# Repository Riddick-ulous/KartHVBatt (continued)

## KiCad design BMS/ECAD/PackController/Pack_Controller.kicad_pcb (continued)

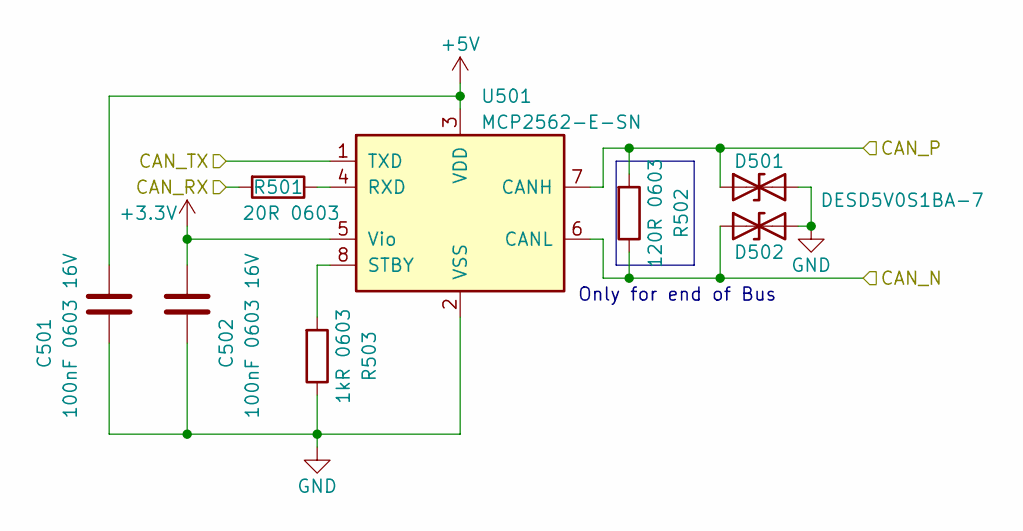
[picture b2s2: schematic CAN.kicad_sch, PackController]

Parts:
C501, C502: 100nF 0603 16V; C_0603_1608Metric_Pad1.08x0.95mm_HandSolder
D501, D502: DESD5V0S1BA-7; D_SOD-323
R501: 20R 0603; R_0603_1608Metric_Pad0.98x0.95mm_HandSolder
R502: 120R 0603; R_0603_1608Metric_Pad0.98x0.95mm_HandSolder
R503: 1kR 0603; R_0603_1608Metric_Pad0.98x0.95mm_HandSolder
U501: MCP2562-E-SN; SOIC-8_3.9x4.9mm_P1.27mm

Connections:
+3.3V: C502.2, U501.5 (Vio); also elsewhere on the board
+5V: C501.2, U501.3 (VDD); also elsewhere on the board
/CAN1/CAN_N: D502.1 (A1), R502.1, U501.6 (CANL); also elsewhere on the board
/CAN1/CAN_P: D501.1 (A1), R502.2, U501.7 (CANH); also elsewhere on the board
/CAN1/CAN_RX: R501.2; also elsewhere on the board
/CAN1/CAN_TX: U501.1 (TXD); also elsewhere on the board
GND: C501.1, C502.1, D501.2 (A2), D502.2 (A2), R503.1, U501.2 (VSS); also elsewhere on the board
unnamed: R501.1, U501.4 (RXD)
unnamed: R503.2, U501.8 (STBY)

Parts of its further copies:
C601, C602: 100nF 0603 16V; C_0603_1608Metric_Pad1.08x0.95mm_HandSolder
D601, D602: DESD5V0S1BA-7; D_SOD-323
R601: 20R 0603; R_0603_1608Metric_Pad0.98x0.95mm_HandSolder
R602: 120R 0603; R_0603_1608Metric_Pad0.98x0.95mm_HandSolder
R603: 1kR 0603; R_0603_1608Metric_Pad0.98x0.95mm_HandSolder
U601: MCP2562-E-SN; SOIC-8_3.9x4.9mm_P1.27mm

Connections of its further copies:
+3.3V: C602.2, U601.5 (Vio); also elsewhere on the board
+5V: C601.2, U601.3 (VDD); also elsewhere on the board
/CAN2/CAN_N: D602.1 (A1), R602.1, U601.6 (CANL); also elsewhere on the board
/CAN2/CAN_P: D601.1 (A1), R602.2, U601.7 (CANH); also elsewhere on the board
/CAN2/CAN_RX: R601.2; also elsewhere on the board
/CAN2/CAN_TX: U601.1 (TXD); also elsewhere on the board
GND: C601.1, C602.1, D601.2 (A2), D602.2 (A2), R603.1, U601.2 (VSS); also elsewhere on the board
unnamed: R601.1, U601.4 (RXD)
unnamed: R603.2, U601.8 (STBY)

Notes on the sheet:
Only for end of Bus

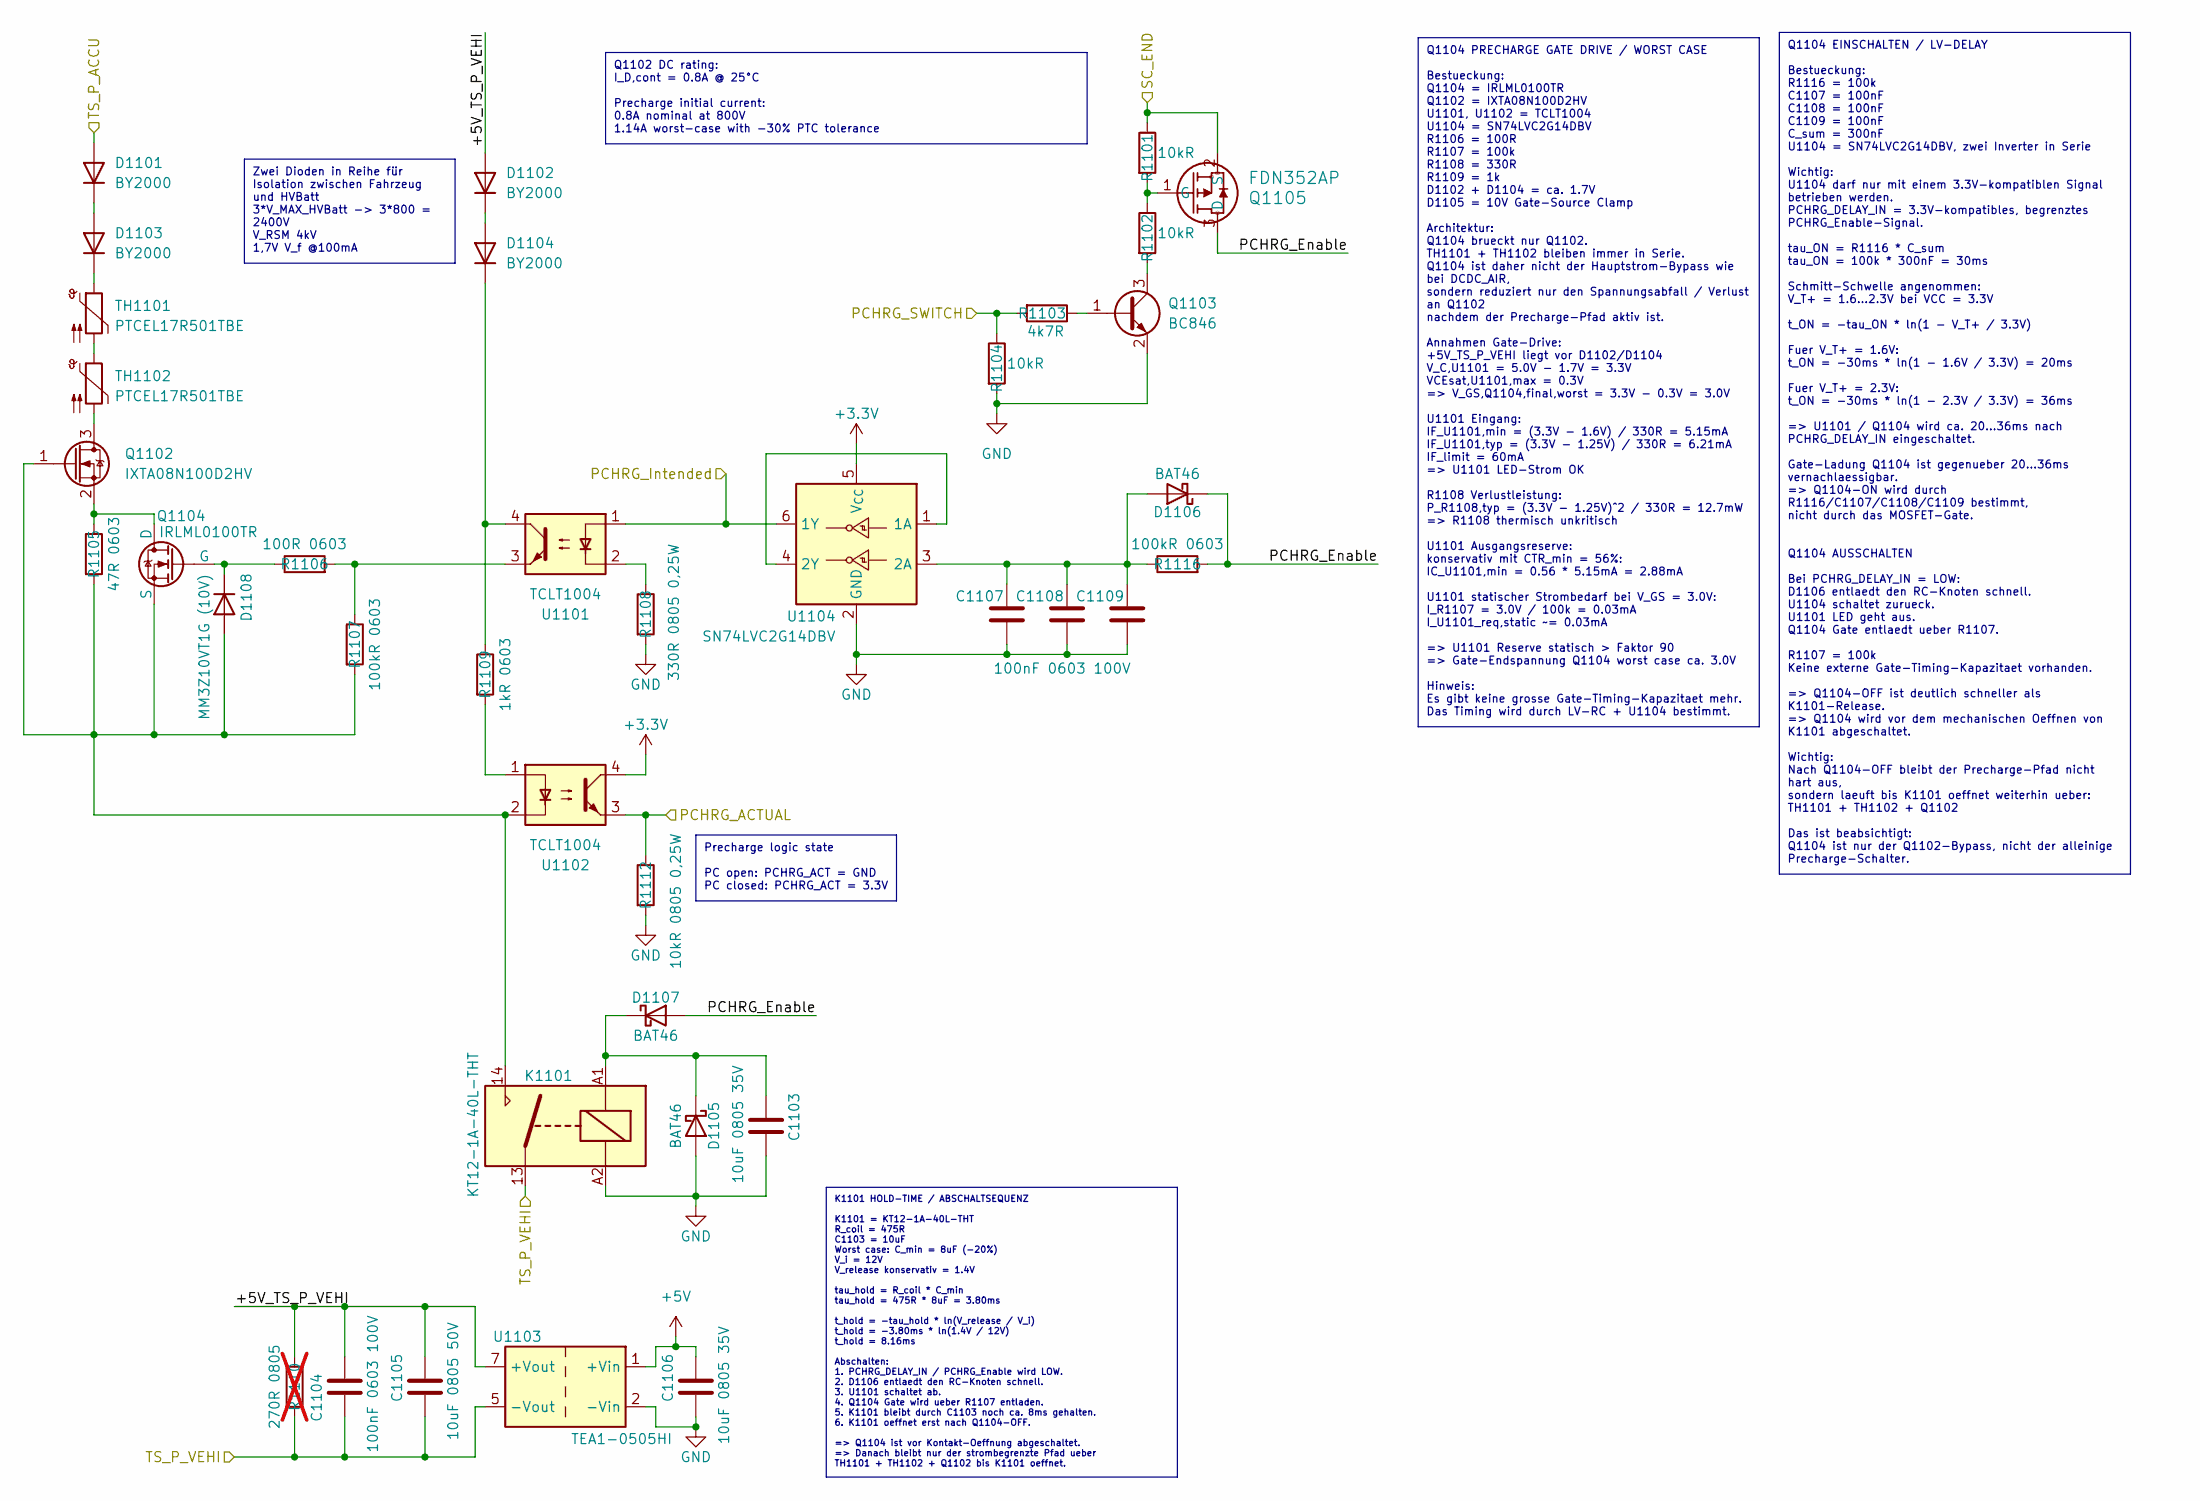
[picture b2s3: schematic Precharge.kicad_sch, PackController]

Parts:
C1103, C1106: 10uF 0805 35V; C_0805_2012Metric
C1104, C1107, C1108, C1109: 100nF 0603 100V; C_0603_1608Metric_Pad1.08x0.95mm_HandSolder
C1105: 10uF 0805 50V; C_0805_2012Metric
D1101, D1102, D1103, D1104: BY2000; D_DO-201AE_P12.70mm_Horizontal
D1105, D1106, D1107: BAT46; D_SOD-123
D1108: MM3Z10VT1G (10V); D_SOD-323_HandSoldering; PartNr. MM3Z3V3T1G
K1101: KT12-1A-40L-THT; Meder_KT_Relay
Q1102: IXTA08N100D2HV; TO-263HV
Q1103: BC846; SOT-23
Q1104: IRLML0100TR; SOT-23-3
Q1105: FDN352AP; SOT-23
R1101, R1102, R1104: 10kR; R_0603_1608Metric
R1103: 4k7R; R_0603_1608Metric
R1105: 47R 0603; R_1206_3216Metric
R1106: 100R 0603; R_0603_1608Metric_Pad0.98x0.95mm_HandSolder
R1107, R1116: 100kR 0603; R_0603_1608Metric_Pad0.98x0.95mm_HandSolder
R1108: 330R 0805 0,25W; R_0805_2012Metric
R1109: 1kR 0603; R_0603_1608Metric_Pad0.98x0.95mm_HandSolder
R1110: 270R 0805; R_0805_2012Metric_Pad1.20x1.40mm_HandSolder; not fitted
R1112: 10kR 0805 0,25W; R_0805_2012Metric
TH1101, TH1102: PTCEL17R501TBE; RV_Disc_D16.5mm_W6.7mm_P7.5mm
U1101, U1102: TCLT1004; SOP-4_7.5x4.1mm_P2.54mm
U1103: TEA1-0505HI; Converter_DCDC_TRACO_TEA1-xxxxHI_THT
U1104: SN74LVC2G14DBV; SOT-23-6

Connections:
+3.3V: U1102.4, U1104.5 (V_{CC}); also elsewhere on the board
+5V: C1106.1, U1103.1 (+Vin); also elsewhere on the board
/AIR/SC_END: Q1105.2 (S), R1101.1; also elsewhere on the board
/MCU/PCHRG_ACTUAL: R1112.1, U1102.3; also elsewhere on the board
/MCU/PCHRG_SWITCH: R1103.2, R1104.1; also elsewhere on the board
/Precharge/+5V_TS_P_VEHI: C1104.2, C1105.1, D1102.2 (A), R1110.2, U1103.7 (+Vout)
/Precharge/PCHRG_Enable: D1106.1 (K), D1107.2 (A), Q1105.3 (D), R1116.2
/Precharge/PCHRG_Intended: U1101.1, U1104.6 (1Y); also elsewhere on the board
/TS_P_ACCU: D1101.2 (A); also elsewhere on the board
/TS_P_VEHI: C1104.1, C1105.2, K1101.13, R1110.1, U1103.5 (-Vout); also elsewhere on the board
GND: C1103.2, C1106.2, C1107.1, C1108.1, C1109.1, D1105.2 (A), K1101.A2, Q1103.2 (E), R1104.2, R1108.2, R1112.2, U1103.2 (-Vin), U1104.2 (GND); also elsewhere on the board
unnamed: D1101.1 (K), D1103.2 (A)
unnamed: D1102.1 (K), D1104.2 (A)
unnamed: D1103.1 (K), TH1101.1
unnamed: D1104.1 (K), R1109.1, U1101.4
unnamed: C1103.1, D1105.1 (K), D1107.1 (K), K1101.A1
unnamed: C1107.2, C1108.2, C1109.2, D1106.2 (A), R1116.1, U1104.3 (2A)
unnamed: D1108.2 (A), K1101.14, Q1102.1 (G), Q1104.3 (S), R1105.2, R1107.2, U1102.2
unnamed: D1108.1 (K), Q1104.2 (G), R1106.1
unnamed: Q1102.3 (D), TH1102.2
unnamed: Q1102.2 (S), Q1104.1 (D), R1105.1
unnamed: Q1103.1 (B), R1103.1
unnamed: Q1103.3 (C), R1102.2
unnamed: Q1105.1 (G), R1101.2, R1102.1
unnamed: R1106.2, R1107.1, U1101.3
unnamed: R1108.1, U1101.2
unnamed: R1109.2, U1102.1
unnamed: TH1101.2, TH1102.1
unnamed: U1104.1 (1A), U1104.4 (2Y)

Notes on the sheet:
Q1104 EINSCHALTEN / LV-DELAY Bestueckung: R1116 = 100k C1107 = 100nF C1108 = 100nF C1109 = 100nF C_sum = 300nF U1104 = SN74LVC2G14DBV, zwei Inverter in Serie Wichtig: U1104 darf nur mit einem 3.3V-kompatiblen Signal betrieben werden. PCHRG_DELAY_IN = 3.3V-kompatibles, begrenztes PCHRG_Enable-Signal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
Q1102 DC rating: I_D,cont = 0.8A @ 25°C Precharge initial current: 0.8A nominal at 800V 1.14A worst-case with -30% PTC tolerance
K1101 HOLD-TIME / ABSCHALTSEQUENZ K1101 = KT12-1A-40L-THT R_coil = 475R C1103 = 10uF Worst case: C_min = 8uF (-20%) V_i = 12V V_release konservativ = 1.4V tau_hold = R_coil * C_min tau_hold = 475R * 8uF = 3.80ms t_hold = -tau_hold * ln(V_release / V_i) t_hold = -3.80ms * ln(1.4V / 12V) t_hold = 8.1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
Q1104 PRECHARGE GATE DRIVE / WORST CASE Bestueckung: Q1104 = IRLML0100TR Q1102 = IXTA08N100D2HV U1101, U1102 = TCLT1004 U1104 = SN74LVC2G14DBV R1106 = 100R R1107 = 100k R1108 = 330R R1109 = 1k D1102 + D1104 = ca. 1.7V D1105 = 10V Gate-Source Clamp Architektur: Q1104 brueckt nur Q1102. TH1101 + TH11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
Zwei Dioden in Reihe für Isolation zwischen Fahrzeug und HVBatt 3*V_MAX_HVBatt -> 3*800 = 2400V V_RSM 4kV 1,7V V_f @100mA
Precharge logic state PC open: PCHRG_ACT = GND PC closed: PCHRG_ACT = 3.3V

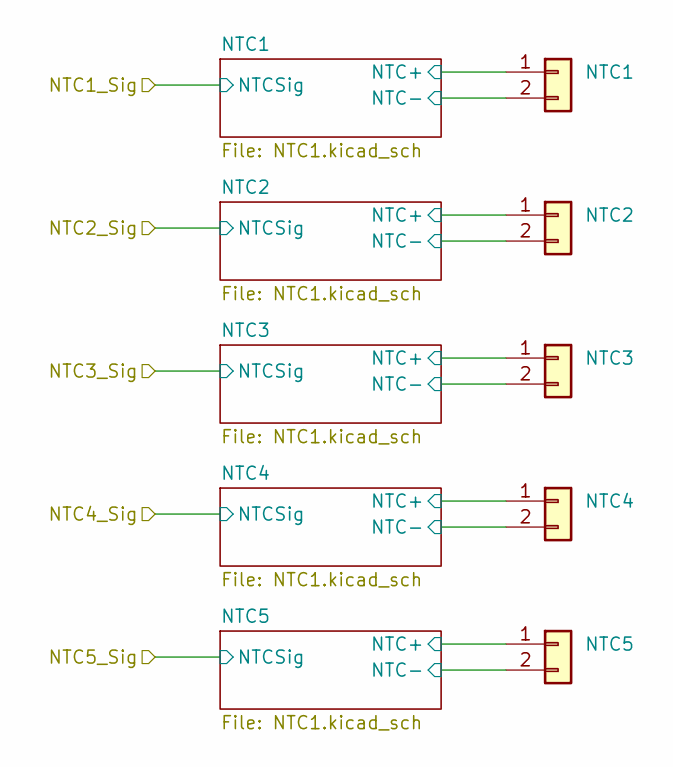
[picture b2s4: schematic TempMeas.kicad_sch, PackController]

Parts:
NTC1, NTC2, NTC3, NTC4, NTC5: Molex_Micro-Fit_3.0_43650-0215_1x02_P3.00mm_Vertical

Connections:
/TempMeas/NTC1/NTC+: NTC1.1; also elsewhere on the board
/TempMeas/NTC2/NTC+: NTC2.1; also elsewhere on the board
/TempMeas/NTC3/NTC+: NTC3.1; also elsewhere on the board
/TempMeas/NTC4/NTC+: NTC4.1; also elsewhere on the board
/TempMeas/NTC5/NTC+: NTC5.1; also elsewhere on the board
GND: NTC1.2, NTC2.2, NTC3.2, NTC4.2, NTC5.2; also elsewhere on the board

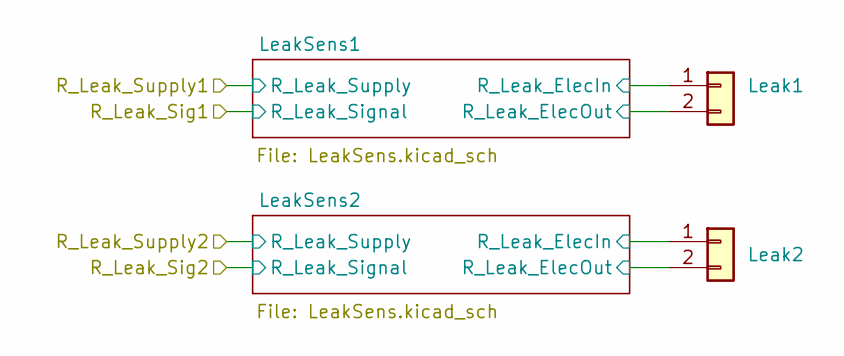
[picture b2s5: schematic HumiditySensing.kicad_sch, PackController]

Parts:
Leak1: Conn_01x02; Molex_Micro-Fit_3.0_43650-0215_1x02_P3.00mm_Vertical
Leak2: Molex_Micro-Fit_3.0_43650-0215_1x02_P3.00mm_Vertical

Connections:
/HumiditySensing/LeakSens1/R_Leak_ElecIn: Leak1.1; also elsewhere on the board
/HumiditySensing/LeakSens1/R_Leak_ElecOut: Leak1.2; also elsewhere on the board
/HumiditySensing/LeakSens2/R_Leak_ElecIn: Leak2.1; also elsewhere on the board
/HumiditySensing/LeakSens2/R_Leak_ElecOut: Leak2.2; also elsewhere on the board

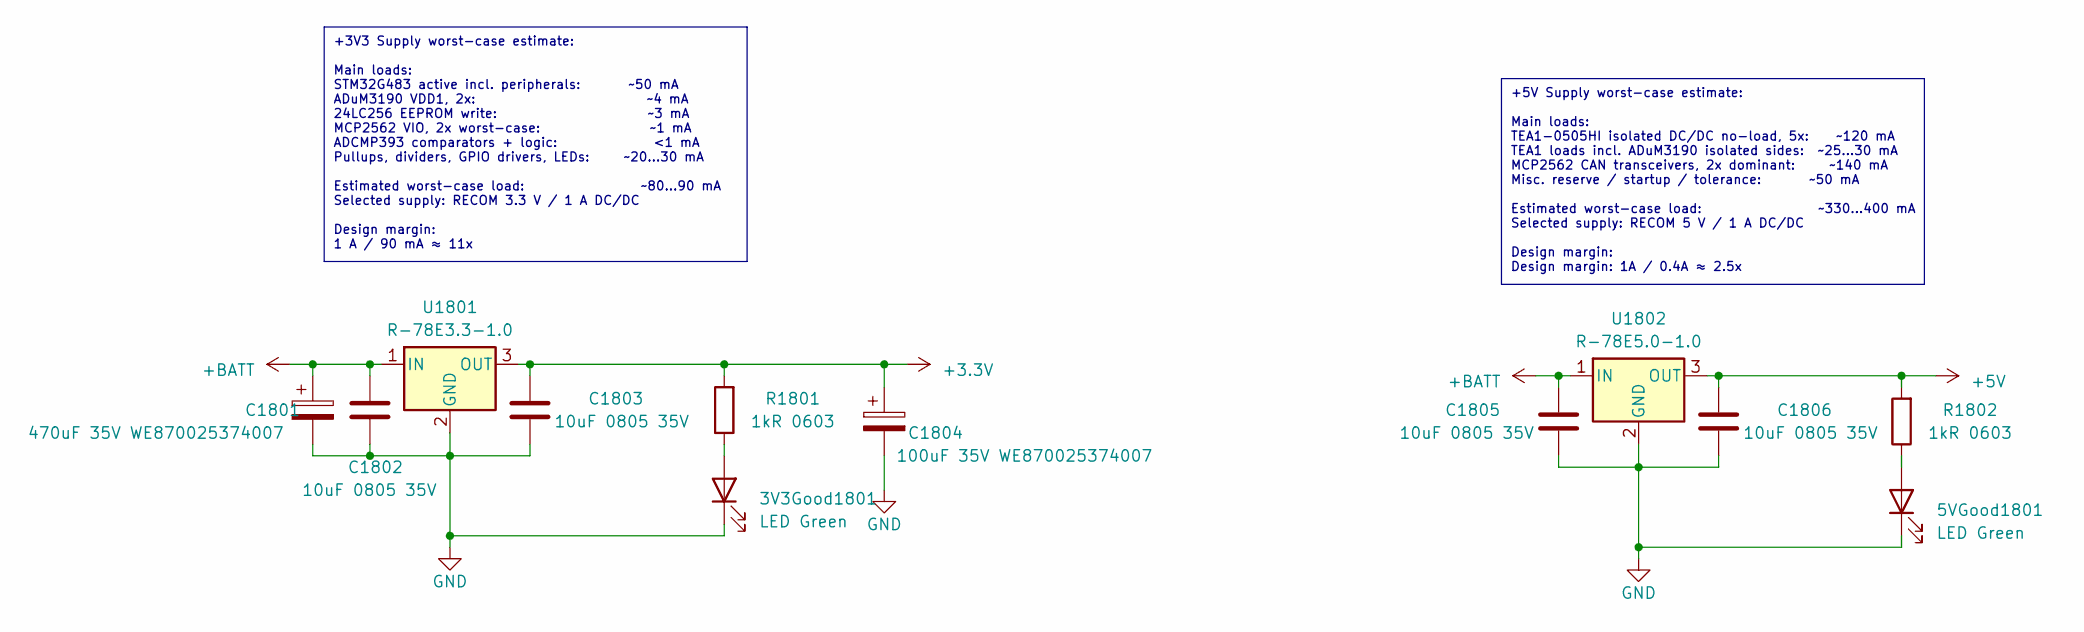
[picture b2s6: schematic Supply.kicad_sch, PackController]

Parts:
3V3Good1801, 5VGood1801: LED Green; LED_0805_2012Metric_Pad1.15x1.40mm_HandSolder
C1801: 470uF 35V WE870025374007; CP_Radial_D8.0mm_P3.50mm
C1802, C1803, C1805, C1806: 10uF 0805 35V; C_0805_2012Metric_Pad1.18x1.45mm_HandSolder
C1804: 100uF 35V WE870025374007; CP_Radial_D8.0mm_P3.50mm
R1801, R1802: 1kR 0603; R_0603_1608Metric_Pad0.98x0.95mm_HandSolder
U1801: R-78E3.3-1.0; Converter_DCDC_RECOM_R-78E-0.5_THT
U1802: R-78E5.0-1.0; Converter_DCDC_RECOM_R-78E-0.5_THT

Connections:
+3.3V: C1803.1, C1804.1, R1801.2, U1801.3 (OUT); also elsewhere on the board
+5V: C1806.1, R1802.2, U1802.3 (OUT); also elsewhere on the board
+BATT: C1801.1, C1802.1, C1805.1, U1801.1 (IN), U1802.1 (IN); also elsewhere on the board
GND: 3V3Good1801.1 (K), 5VGood1801.1 (K), C1801.2, C1802.2, C1803.2, C1804.2, C1805.2, C1806.2, U1801.2 (GND), U1802.2 (GND); also elsewhere on the board
unnamed: 3V3Good1801.2 (A), R1801.1
unnamed: 5VGood1801.2 (A), R1802.1

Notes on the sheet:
+3V3 Supply worst-case estimate: Main loads: STM32G483 active incl. peripherals: ~50 mA ADuM3190 VDD1, 2x: ~4 mA 24LC256 EEPROM write: ~3 mA MCP2562 VIO, 2x worst-case: ~1 mA ADCMP393 comparators + logic: <1 mA Pullups, dividers, GPIO drivers, LEDs: ~20...30 mA Estimated worst-case load: ~80...90 m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
+5V Supply worst-case estimate: Main loads: TEA1-0505HI isolated DC/DC no-load, 5x: ~120 mA TEA1 loads incl. ADuM3190 isolated sides: ~25...30 mA MCP2562 CAN transceivers, 2x dominant: ~140 mA Misc. reserve / startup / tolerance: ~50 mA Estimated worst-case load: ~330...400 mA Selected supply: RECO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

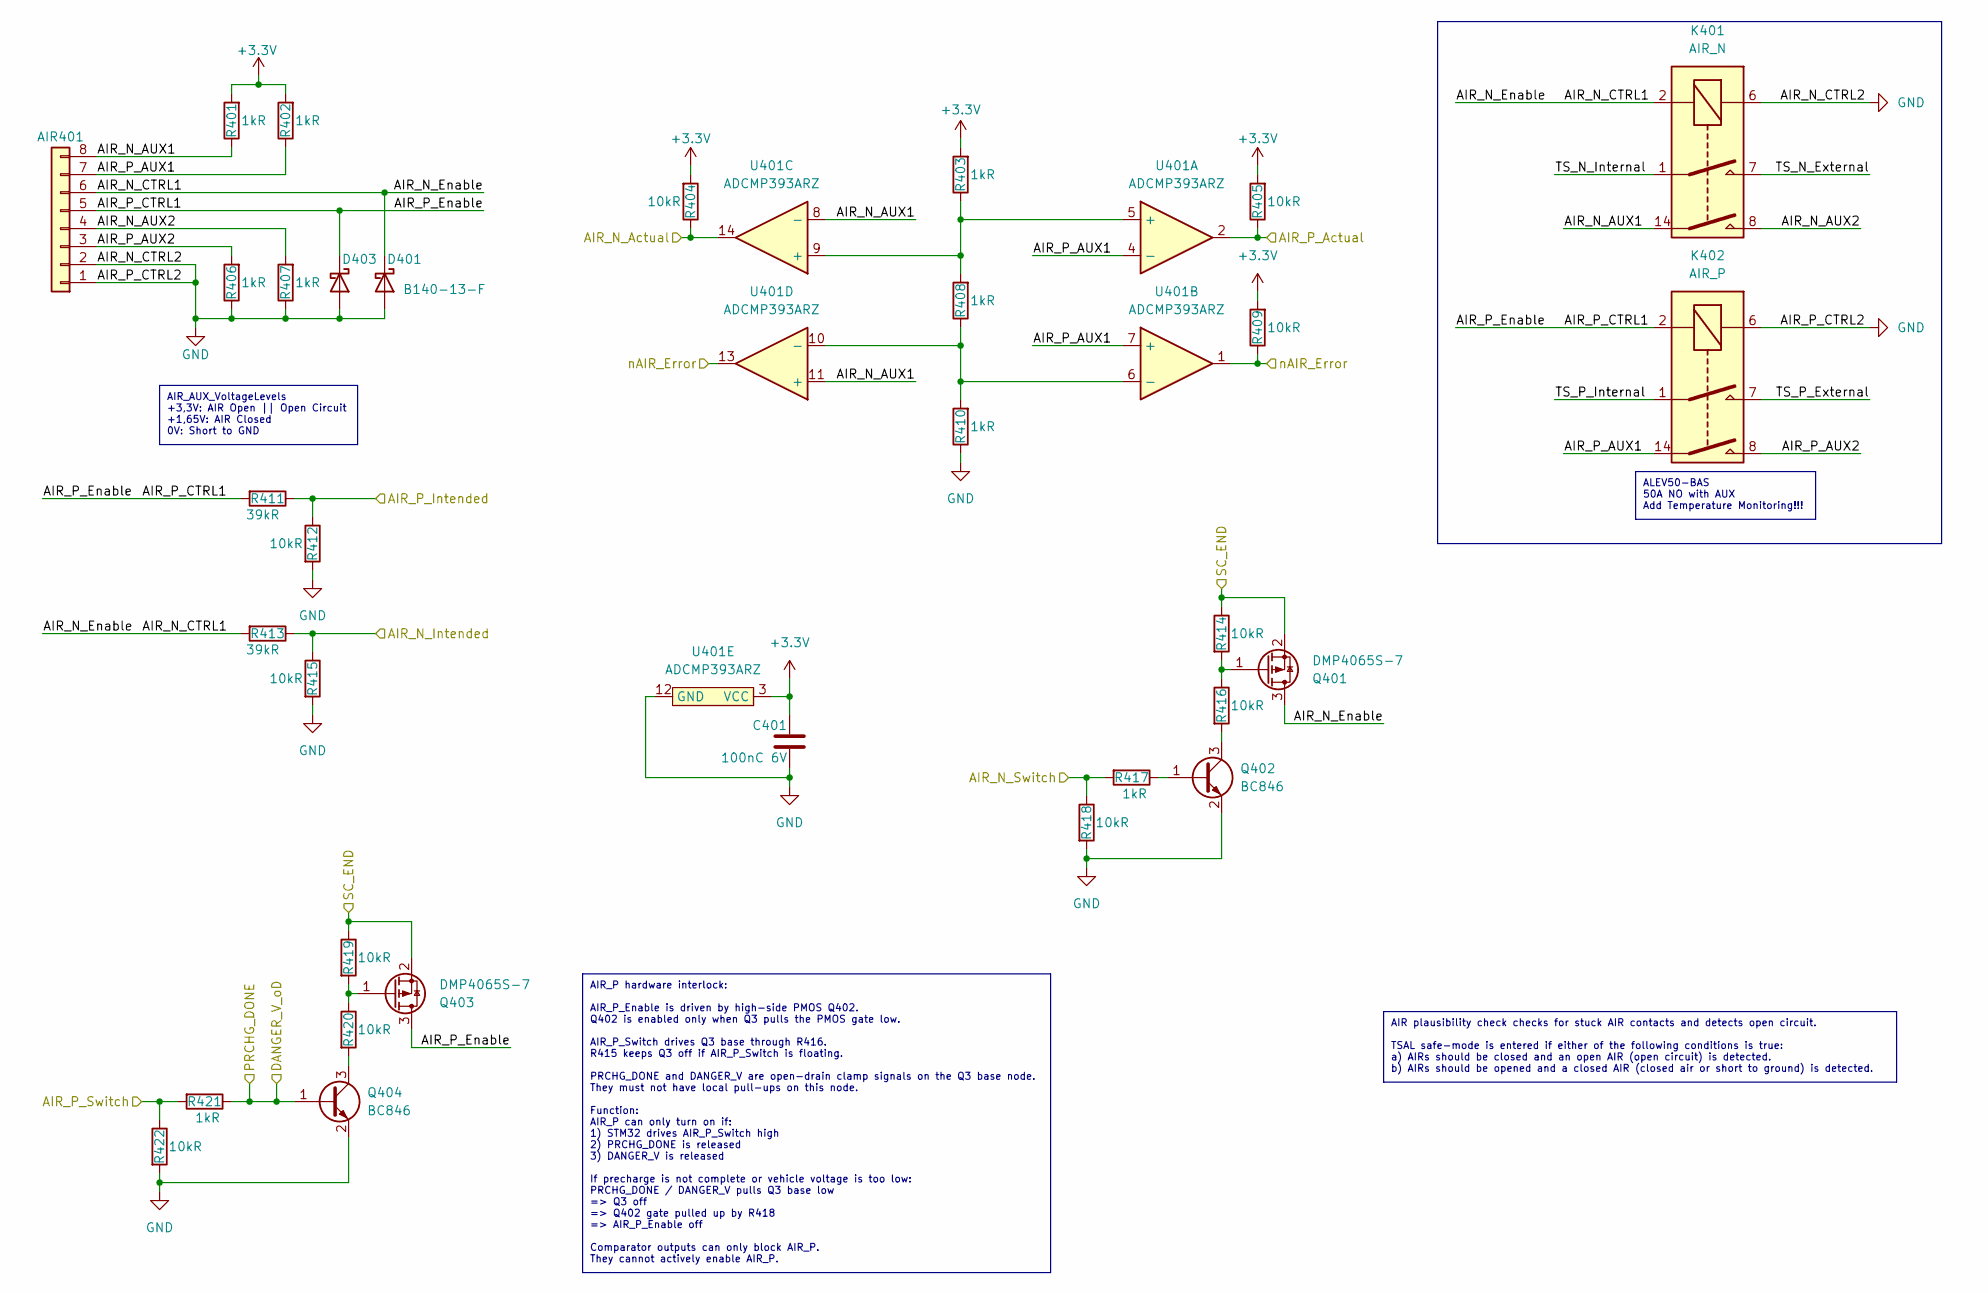
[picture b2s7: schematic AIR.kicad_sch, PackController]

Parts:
AIR401: Molex_Micro-Fit_3.0_43045-0812_2x04_P3.00mm_Vertical
C401: 100nC 6V; C_0603_1608Metric
D401, D403: B140-13-F; D_SMA
K401: AIR_N
K402: AIR_P
Q401, Q403: DMP4065S-7; SOT-23-3
Q402, Q404: BC846; SOT-23
R401, R402, R403, R406, R407, R408, R410, R417, R421: 1kR; R_0603_1608Metric
R404, R405, R409, R412, R414, R415, R416, R418, R419, R420, R422: 10kR; R_0603_1608Metric
R411, R413: 39kR; R_0603_1608Metric
U401: ADCMP393ARZ; SOIC-14_3.9x8.7mm_P1.27mm

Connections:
+3.3V: C401.1, R401.2, R402.2, R403.2, R404.2, R405.2, R409.2, U401.3 (VCC); also elsewhere on the board
/AIR/AIR_N_AUX1: AIR401.8, K401.14, R401.1, U401.8 (-), U401.11 (+)
/AIR/AIR_N_AUX2: AIR401.4, K401.8, R407.2
/AIR/AIR_N_Actual: R404.1, U401.14; also elsewhere on the board
/AIR/AIR_N_CTRL1: AIR401.6, D401.1 (K), K401.2, Q401.3 (D), R413.2
/AIR/AIR_N_Intended: R413.1, R415.1; also elsewhere on the board
/AIR/AIR_N_Switch: R417.2, R418.1; also elsewhere on the board
/AIR/AIR_P_AUX1: AIR401.7, K402.14, R402.1, U401.4 (-), U401.7 (+)
/AIR/AIR_P_AUX2: AIR401.3, K402.8, R406.2
/AIR/AIR_P_Actual: R405.1, U401.2; also elsewhere on the board
/AIR/AIR_P_CTRL1: AIR401.5, D403.1 (K), K402.2, Q403.3 (D), R411.2
/AIR/AIR_P_Intended: R411.1, R412.1; also elsewhere on the board
/AIR/AIR_P_Switch: R421.2, R422.1; also elsewhere on the board
/AIR/DANGER_V_oD: Q404.1 (B), R421.1; also elsewhere on the board
/AIR/SC_END: Q401.2 (S), Q403.2 (S), R414.1, R419.1; also elsewhere on the board
/AIR/nAIR_Error: R409.1, U401.1, U401.13; also elsewhere on the board
GND: AIR401.1, AIR401.2, C401.2, D401.2 (A), D403.2 (A), K401.6, K402.6, Q402.2 (E), Q404.2 (E), R406.1, R407.1, R410.1, R412.2, R415.2, R418.2, R422.2, U401.12 (GND); also elsewhere on the board
unnamed: Q401.1 (G), R414.2, R416.1
unnamed: Q402.1 (B), R417.1
unnamed: Q402.3 (C), R416.2
unnamed: Q403.1 (G), R419.2, R420.1
unnamed: Q404.3 (C), R420.2
unnamed: R403.1, R408.2, U401.5 (+), U401.9 (+)
unnamed: R408.1, R410.2, U401.6 (-), U401.10 (-)

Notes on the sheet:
AIR plausibility check checks for stuck AIR contacts and detects open circuit. TSAL safe-mode is entered if either of the following conditions is true: a) AIRs should be closed and an open AIR (open circuit) is detected. b) AIRs should be opened and a closed AIR (closed air or short to ground) is d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
ALEV50-BAS 50A NO with AUX Add Temperature Monitoring!!!
AIR_P hardware interlock: AIR_P_Enable is driven by high-side PMOS Q402. Q402 is enabled only when Q3 pulls the PMOS gate low. AIR_P_Switch drives Q3 base through R416. R415 keeps Q3 off if AIR_P_Switch is floating. PRCHG_DONE and DANGER_V are open-drain clamp signals on the Q3 base node. They must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
AIR_AUX_VoltageLevels +3,3V: AIR Open || Open Circuit +1,65V: AIR Closed 0V: Short to GND

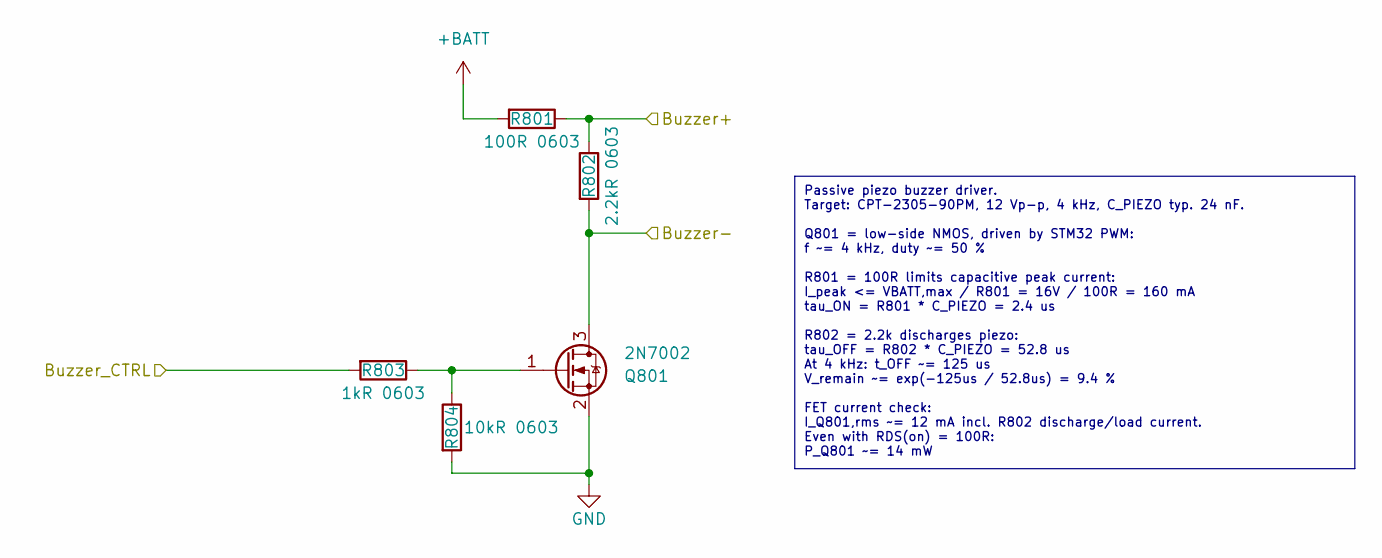
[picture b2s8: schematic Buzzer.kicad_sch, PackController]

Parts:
Q801: 2N7002; SOT-23
R801: 100R 0603; R_0603_1608Metric_Pad0.98x0.95mm_HandSolder
R802: 2.2kR 0603; R_0603_1608Metric_Pad0.98x0.95mm_HandSolder
R803: 1kR 0603; R_0603_1608Metric_Pad0.98x0.95mm_HandSolder
R804: 10kR 0603; R_0603_1608Metric_Pad0.98x0.95mm_HandSolder

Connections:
+BATT: R801.2; also elsewhere on the board
/Buzzer/Buzzer+: R801.1, R802.1; also elsewhere on the board
/Buzzer/Buzzer-: Q801.3 (D), R802.2; also elsewhere on the board
/Buzzer/Buzzer_CTRL: R803.2; also elsewhere on the board
GND: Q801.2 (S), R804.2; also elsewhere on the board
unnamed: Q801.1 (G), R803.1, R804.1

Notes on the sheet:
Passive piezo buzzer driver. Target: CPT-2305-90PM, 12 Vp-p, 4 kHz, C_PIEZO typ. 24 nF. Q801 = low-side NMOS, driven by STM32 PWM: f ~= 4 kHz, duty ~= 50 % R801 = 100R limits capacitive peak current: I_peak <= VBATT,max / R801 = 16V / 100R = 160 mA tau_ON = R801 * C_PIEZO = 2.4 us R802 = 2.2k disch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

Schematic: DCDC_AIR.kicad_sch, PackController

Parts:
C1901, C1902, C1903, C1907: 100nF 0603 100V; C_0603_1608Metric_Pad1.08x0.95mm_HandSolder
C1904, C1905, C1906: 10uF 0805 35V; C_0805_2012Metric
D1901, D1905, D1906: BAT46; D_SOD-123
D1902: MM3Z10VT1G (10V); D_SOD-323_HandSoldering; PartNr. MM3Z3V3T1G
D1903: BY2000; D_DO-201AE_P12.70mm_Horizontal
F1901: 2,5A 800V 0ADBP2500-RE; R_Axial_Power_L38.0mm_W6.4mm_P40.64mm
K1901: KT12-1A-40L-THT; Meder_KT_Relay
Q1901: IXTA08N100D2HV; TO-263HV
Q1902: IPD95R750P7; TO-252-2
Q1903: BC846; SOT-23
Q1905: FDN352AP; SOT-23
R1901: 47R 0603; R_1206_3216Metric
R1902: 100R 0603; R_0603_1608Metric_Pad0.98x0.95mm_HandSolder
R1903, R1909: 100kR 0603; R_0603_1608Metric_Pad0.98x0.95mm_HandSolder
R1904: 1kR 0603; R_0603_1608Metric_Pad0.98x0.95mm_HandSolder
R1905: 330R 0805 0,25W; R_0805_2012Metric
R1906: 10kR 0805 0,25W; R_0805_2012Metric
R1907, R1911, R1912: 10kR; R_0603_1608Metric
R1908: 4k7R; R_0603_1608Metric
R1910: 270R 0805; R_0805_2012Metric_Pad1.20x1.40mm_HandSolder; not fitted
TH1901, TH1902: PTCEL17R501TBE; RV_Disc_D16.5mm_W6.7mm_P7.5mm
U1901, U1902: TCLT1004; SOP-4_7.5x4.1mm_P2.54mm
U1903: TEA1-0505HI; Converter_DCDC_TRACO_TEA1-xxxxHI_THT
U1904: SN74LVC2G14DBV; SOT-23-6

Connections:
+3.3V: U1902.4, U1904.5 (V_{CC}); also elsewhere on the board
+5V: C1905.1, U1903.1 (+Vin); also elsewhere on the board
/AIR/SC_END: Q1905.2 (S), R1911.1; also elsewhere on the board
/DCDC_AIR/+5V_TS_P_DCDC: C1903.2, C1904.1, D1903.2 (A), R1910.2, U1903.7 (+Vout)
/DCDC_AIR/DCDC_AIR_ACTUAL: R1906.1, U1902.3; also elsewhere on the board
/DCDC_AIR/DCDC_AIR_Enable: D1901.1 (K), D1905.2 (A), Q1905.3 (D), R1909.2
/DCDC_AIR/DCDC_AIR_SWITCH: R1907.1, R1908.2; also elsewhere on the board
/DCDC_AIR/TS_P_DCDC: C1903.1, C1904.2, K1901.13, R1910.1, U1903.5 (-Vout); also elsewhere on the board
/TS_P_ACCU: F1901.1; also elsewhere on the board
GND: C1901.1, C1902.1, C1905.2, C1906.2, C1907.1, D1906.2 (A), K1901.A2, Q1903.2 (E), R1905.2, R1906.2, R1907.2, U1903.2 (-Vin), U1904.2 (GND); also elsewhere on the board
unnamed: C1901.2, C1902.2, C1907.2, D1901.2 (A), R1909.1, U1904.3 (2A)
unnamed: D1902.2 (A), K1901.14, Q1901.1 (G), Q1902.3 (S), R1901.2, R1903.2, U1902.2
unnamed: D1902.1 (K), Q1902.2 (G), R1902.1
unnamed: D1903.1 (K), R1904.1, U1901.4
unnamed: C1906.1, D1905.1 (K), D1906.1 (K), K1901.A1
unnamed: Q1901.3 (D), TH1902.2
unnamed: Q1901.2 (S), R1901.1
unnamed: F1901.2, Q1902.1 (D), TH1901.1
unnamed: Q1903.1 (B), R1908.1
unnamed: Q1903.3 (C), R1912.2
unnamed: Q1905.1 (G), R1911.2, R1912.1
unnamed: R1902.2, R1903.1, U1901.3
unnamed: R1904.2, U1902.1
unnamed: R1905.1, U1901.2
unnamed: TH1901.2, TH1902.1
unnamed: U1904.1 (1A), U1904.4 (2Y)
unnamed: U1901.1, U1904.6 (1Y)

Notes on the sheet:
Q1902 Gate-Ladung: IPD95R750P7: Qg,total,typ = 23nC @ V_GS = 0...10V Ciss,typ = 712pF U1901 Ausgangsstromreserve: IC_U1901,min ~= 8.2mA Statischer Laststrom durch R1903 + U1902 ~= 3.2mA Verbleibender Gate-Ladestrom > 5mA t_gate_on ~= Qg / I_gate t_gate_on ~= 23nC / 5mA = 4.6us => Gate-Ladung ist ge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
Q1902 Ausschalten: D1901 entlaedt den RC-Knoten bei DCDC_AIR_Enable = LOW schnell unter V_T- von U1904. U1904 schaltet zurueck, U1901 LED geht aus. Q1902 Gate entlaedt ueber R1903. Konservative Gate-Entladung: Qg,total,typ = 23nC R1903 = 100k I_discharge,start ~= 4.7V / 100k = 47uA t_gate_off ~= Qg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
K1901 Hold-Time / Abschaltsequenz: K1901 = KT12-1A-40L-THT R_coil = 475R C1906 = 10uF Worst case: C_min = 8uF (-20%) V_i = 12V V_release konservativ = 1.4V tau_hold = R_coil * C_min tau_hold = 475R * 8uF = 3.80ms t_hold = -tau_hold * ln(V_release / V_i) t_hold = -3.80ms * ln(1.4V / 12V) t_hold = 8.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
DCDC AIR logic state DCDC_AIR open: DCDC_AIR_ACT = GND DCDC_AIR closed: DCDC_AIR_ACT = 3.3V
Q1901 DC rating: I_D,cont = 0.8A @ 25°C Precharge initial current: 0.8A nominal at 800V 1.14A worst-case with -30% PTC tolerance
Q1902 DCDC_AIR GATE DRIVE / WORST CASE Bestueckung: Q1902 = IPD95R750P7 U1901, U1902 = TCLT1004 U1904 = SN74LVC2G14DBV R1902 = 100R R1903 = 100k R1904 = 1k R1905 = 330R R1906 = 10k D1902 = Gate-Source-Zener/TVS ca. 7...10V IPD95R750P7: V_DS,max = 950V V_GS(th) = 2.5...3.5V V_plateau,typ = 4.4V R_DS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

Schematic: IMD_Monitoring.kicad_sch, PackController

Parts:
C2301: 10uF 0805 35V; C_0805_2012Metric
C2302: 100nC 16V; C_0603_1608Metric
D2301, D2302, D2303: BAT46; D_SOD-123
Q2301: BC846; SOT-23
Q2302: DMP4065S-7; SOT-23-3
R2301: 1.5MR; R_0603_1608Metric_Pad0.98x0.95mm_HandSolder
R2302, R2303, R2304: See Note; R_0603_1608Metric_Pad0.98x0.95mm_HandSolder
R2305: 39kR; R_0603_1608Metric_Pad0.98x0.95mm_HandSolder
R2306, R2307, R2308: 10kR; R_0603_1608Metric_Pad0.98x0.95mm_HandSolder
R2310: 1kR; R_0603_1608Metric_Pad0.98x0.95mm_HandSolder
U2301: SN74LVC1G74; VSSOP-8_2.3x2mm_P0.5mm
U2303: SN74LVC2G17DCK; SOT-23-6

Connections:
+3.3V: C2302.1, D2302.1 (K), R2301.1, R2304.2, R2310.1, U2301.4 (GND), U2303.5 (V_{CC}); also elsewhere on the board
/IMD_Monitoring/IMD_OK: R2305.2, R2306.2, U2303.3 (2A); also elsewhere on the board
/IMD_Monitoring/IMD_SC_Closed: D2301.2 (A), D2303.2 (A), Q2301.1 (B), R2310.2; also elsewhere on the board
/IMD_Monitoring/IMD_State: R2302.2, R2303.2, R2304.1; also elsewhere on the board
/IMD_Monitoring/M_HSLS: R2302.1; also elsewhere on the board
/IMD_Monitoring/OK_HS: R2305.1; also elsewhere on the board
/IMD_Monitoring/SC_In: Q2302.3 (S), R2307.1; also elsewhere on the board
/IMD_Monitoring/SC_Out: Q2302.1 (D); also elsewhere on the board
GND: C2301.1, C2302.2, Q2301.2 (E), R2303.1, R2306.1, U2301.1 (CLK), U2301.2 (D), U2301.8 (VCC), U2303.2 (GND); also elsewhere on the board
unnamed: D2301.1 (K), U2301.5 (Q)
unnamed: C2301.2, D2302.2 (A), R2301.2, U2303.1 (1A)
unnamed: D2303.1 (K), U2301.6 (nCLR), U2303.4 (2Y)
unnamed: Q2301.3 (C), R2308.2
unnamed: Q2302.2 (G), R2307.2, R2308.1
unnamed: U2301.7 (nPRE), U2303.6 (1Y)

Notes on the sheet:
During IMD startup, nPRE and nCLR may overlap. SC_Out is forced disabled by IMD_OK low clamp. Latch becomes effective only after IMD_OK release.
Populate pullup/-down depending on IMD type: Open-Collector: 10k Pullup + 0Ohm series resistor Open-Emitter: 1k5 Pulldown + 10kOhm series resistor (Use Variants to see on schematic)

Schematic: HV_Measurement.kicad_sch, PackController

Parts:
C901: 100n 0603 50V; C_0603_1608Metric
C916, C919, C928, C931: 100nF 0603 100V; C_0603_1608Metric_Pad1.08x0.95mm_HandSolder
C917, C929: 1uF 0805 50V; C_0805_2012Metric
C918, C930: 100pC 0603 50V; C_0603_1608Metric
C920, C932: 1uC 0805 50V; C_0805_2012Metric
C921, C926, C933, C938: 100nC 0603 50V; C_0603_1608Metric
C922, C923, C934: 10uF 0805 35V; C_0805_2012Metric
C924, C936: 100nC 0603 16V; C_0603_1608Metric
C925, C937: 1uC 0805 16V; C_0805_2012Metric
C927, C939: 1nC 0603 16V; C_0603_1608Metric
C935: 10uF 0805 50V; C_0805_2012Metric
R901: 68.1K 0.1%; R_0603_1608Metric_Pad0.98x0.95mm_HandSolder
R902, R904: 270R 0805; R_0805_2012Metric_Pad1.20x1.40mm_HandSolder
R903: 3.9k 0.1%; R_0603_1608Metric_Pad0.98x0.95mm_HandSolder
R905: 909kR 0.1%; R_0603_1608Metric_Pad0.98x0.95mm_HandSolder
R909, R920: 10kR; R_0603_1608Metric_Pad0.98x0.95mm_HandSolder
R917: 100kR 0.1%; R_0603_1608Metric_Pad0.98x0.95mm_HandSolder
R921, R922, R925, R926: 4.7MR 2512 3kV 0,1%; R_2512_6332Metric_Pad1.40x3.35mm_HandSolder
R923, R927: 26.1kR 2512 500V 0,1%; R_2512_6332Metric_Pad1.40x3.35mm_HandSolder
R924, R928: 1kR; R_0603_1608Metric_Pad0.98x0.95mm_HandSolder
U901: ADCMP393ARZ; SOIC-14_3.9x8.7mm_P1.27mm
U906, U909: LP5907MFX-3.3; SOT-23-5
U907, U910: AMC0311R; AMC0311R Wide-body SOIC (DWV)
U908, U911: TEA1-0505HI; Converter_DCDC_TRACO_TEA1-xxxxHI_THT

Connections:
+3.3V: C901.1, C926.1, C938.1, R901.1, R909.1, R920.1, U901.3 (VCC), U907.6 (REFIN), U910.6 (REFIN); also elsewhere on the board
+3.3V_ACCU: C916.2, C917.1, C920.1, C921.1, U906.5 (OUT), U907.1 (VDD1)
+3.3V_VEHI: C928.2, C929.1, C932.1, C933.1, U909.5 (OUT), U910.1 (VDD1)
+5V: C923.1, C924.1, C925.1, C935.1, C936.1, C937.1, U907.8 (VDD2), U908.1 (+Vin), U910.8 (VDD2), U911.1 (+Vin); also elsewhere on the board
+5V_ACCU: C919.2, C922.1, R902.2, U906.1 (IN), U906.3 (EN), U908.7 (+Vout)
+5V_VEHI: C931.2, C934.1, R904.2, U909.1 (IN), U909.3 (EN), U911.7 (+Vout)
/AIR/DANGER_V_oD: U901.1, U901.14; also elsewhere on the board
/HV_Measurement/V_ACCU: C927.1, R917.1, R924.1; also elsewhere on the board
/HV_Measurement/V_VEHI: C939.1, R928.1, U901.4 (-), U901.7 (+), U901.9 (+), U901.10 (-); also elsewhere on the board
/HV_Measurement/nDANGER_V: R909.2, U901.2; also elsewhere on the board
/HV_Measurement/nPRCHG_DONE: R920.2, U901.13; also elsewhere on the board
/TS_N_ACCU: C916.1, C917.2, C918.2, C919.1, C920.2, C921.2, C922.2, R902.1, R923.2, U906.2 (GND), U907.3 (SNSN), U907.4 (GND1), U908.5 (-Vout); also elsewhere on the board
/TS_N_VEHI: C928.1, C929.2, C930.2, C931.1, C932.2, C933.2, C934.2, R904.1, R927.2, U909.2 (GND), U910.3 (SNSN), U910.4 (GND1), U911.5 (-Vout); also elsewhere on the board
/TS_P_ACCU: R921.1; also elsewhere on the board
/TS_P_VEHI: R925.1; also elsewhere on the board
GND: C901.2, C923.2, C924.2, C925.2, C926.2, C927.2, C935.2, C936.2, C937.2, C938.2, C939.2, R903.2, R905.2, U901.12 (GND), U907.5 (GND2), U908.2 (-Vin), U910.5 (GND2), U911.2 (-Vin); also elsewhere on the board
unnamed: R921.2, R922.1
unnamed: R925.2, R926.1
unnamed: R901.2, R903.1, U901.5 (+), U901.6 (-)
unnamed: R905.1, R917.2, U901.8 (-), U901.11 (+)
unnamed: C918.1, R922.2, R923.1, U907.2 (INP)
unnamed: R924.2, U907.7 (OUT)
unnamed: C930.1, R926.2, R927.1, U910.2 (INP)
unnamed: R928.2, U910.7 (OUT)

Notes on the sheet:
AMC0311R TRANSFER FUNCTION V_REFIN = 3.3 V V_CLIP = 2.56 V G_AMC = V_REFIN / V_CLIP G_AMC = 3.3 V / 2.56 V G_AMC = 1.28906 V/V V_OUT = V_INP * G_AMC V_OUT = V_HV * k_DIV * G_AMC V_OUT = V_HV * 0.00356929 V_OUT = V_HV / 280.167 V_HV = V_OUT * 280.167 V_OUT @ 40 V = 0.143 V V_OUT @ 588 V = 2.099 V V_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
AMC INPUT LOW-PASS R_TH = R_TOP || R_SNS R_TH = 9.4 MOhm || 26.1 kOhm R_TH approx. 26.03 kOhm C_IN = C2004 = 100 pF tau_IN = R_TH * C_IN tau_IN approx. 2.60 us f_c,IN = 1 / (2 * pi * R_TH * C_IN) f_c,IN approx. 61.1 kHz t_10-90,IN approx. 2.2 * tau_IN t_10-90,IN approx. 5.7 us AMC OUTPUT / ADC LOW-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
PRECHARGE 90 % CHECK / HARDWARE CLAMP V_ACCU and V_VEHI are nominally equally scaled isolated HV measurements. 90 % reference divider: R_SER = 100 kOhm R_GND = 909 kOhm k_90 = R_GND / (R_SER + R_GND) k_90 = 909 k / (100 k + 909 k) k_90 = 0.900892 V_ACCU_90 = k_90 * V_ACCU PRCHG_DONE: IN+ = V_VEHI I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
4.4mm creepage per R for 2512 inch package
DANGER VOLTAGE THRESHOLD: APPROX. 50 V HV measurement transfer: R_TOP = 4.7 MOhm + 4.7 MOhm = 9.4 MOhm R_SNS = 26.1 kOhm k_DIV = 26.1 k / (9.4 M + 26.1 k) k_DIV = 0.00276891 AMC0311R: V_OUT = V_HV * k_DIV * V_REFIN / 2.56 V With V_REFIN = 3.3 V: V_OUT = V_HV * 0.00356930 V_OUT @ 50 V = 178.46 mV Co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
HV ACCU VOLTAGE DIVIDER / 0...800 V R_TOP = R2004 + R2005 R_TOP = 4.7 MOhm + 4.7 MOhm = 9.4 MOhm R_SNS = R2006 = 26.1 kOhm k_DIV = R_SNS / (R_TOP + R_SNS) k_DIV = 26.1 k / (9.4 M + 26.1 k) k_DIV = 0.00276891 = 1 / 361.153 V_INP = V_HV * k_DIV V_INP @ 588 V = 1.628 V V_INP @ 800 V = 2.215 V AMC0311R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
PRCHG_DONE = open-drain hardware clamp only nPRCHG_DONE = MCU-readable status
DANGER_V_oD is open-drain clamp only, not MCU logic. Use nDANGER_V for MCU diagnostics.
